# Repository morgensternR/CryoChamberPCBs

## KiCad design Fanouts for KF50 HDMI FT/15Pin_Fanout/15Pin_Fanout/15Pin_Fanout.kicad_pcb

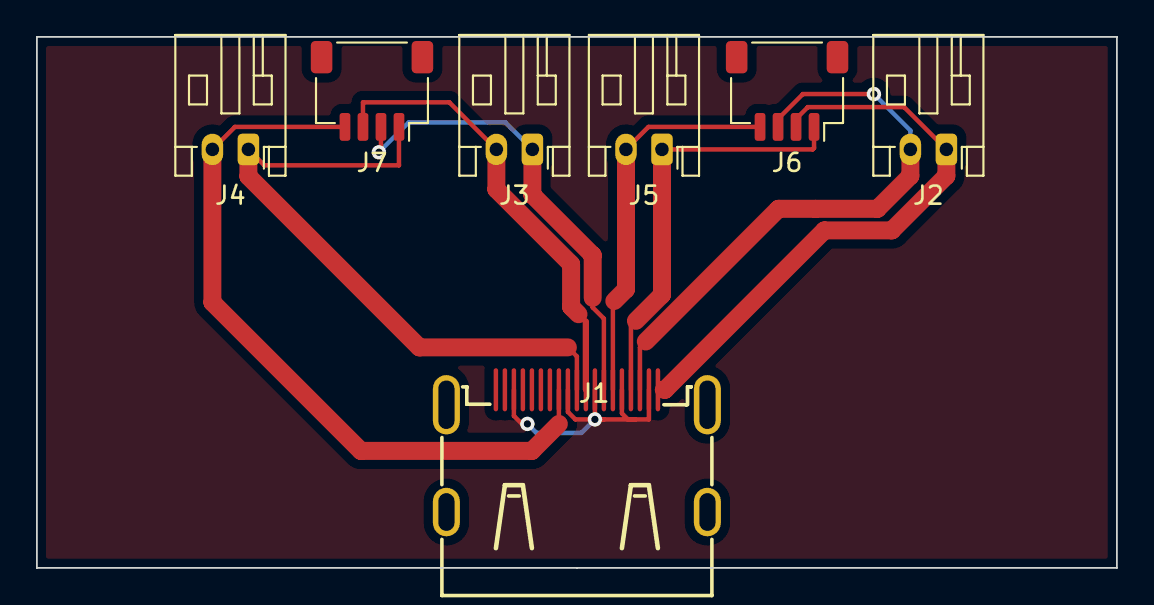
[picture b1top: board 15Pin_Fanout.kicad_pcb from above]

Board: 2 copper layers, 60.0 x 29.5 mm, 7 parts (0 on the bottom side), 9 nets.

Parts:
J1: HDMI_A; HDMI-SMD_HDMI-019S
J2, J3, J4, J5: Conn_01x02; JST_PH_S2B-PH-K_1x02_P2.00mm_Horizontal
J6, J7: Conn_01x04; JST_SH_SM04B-SRSS-TB_1x04-1MP_P1.00mm_Horizontal

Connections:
GND: J1.2 (D2S), J1.5 (D1S), J1.8 (D0S), J1.11 (CKS), J1.17 (GND)
unnamed: J1.1 (D2+), J2.1, J6.2
unnamed: J1.3 (D2-), J2.2, J6.3
unnamed: J1.4 (D1+), J5.1, J6.1
unnamed: J1.6 (D1-), J5.2, J6.4
unnamed: J1.7 (D0+), J3.1, J7.2
unnamed: J1.9 (D0-), J3.2, J7.3
unnamed: J1.10 (CK+), J4.1, J7.1
unnamed: J1.12 (CK-), J4.2, J7.4

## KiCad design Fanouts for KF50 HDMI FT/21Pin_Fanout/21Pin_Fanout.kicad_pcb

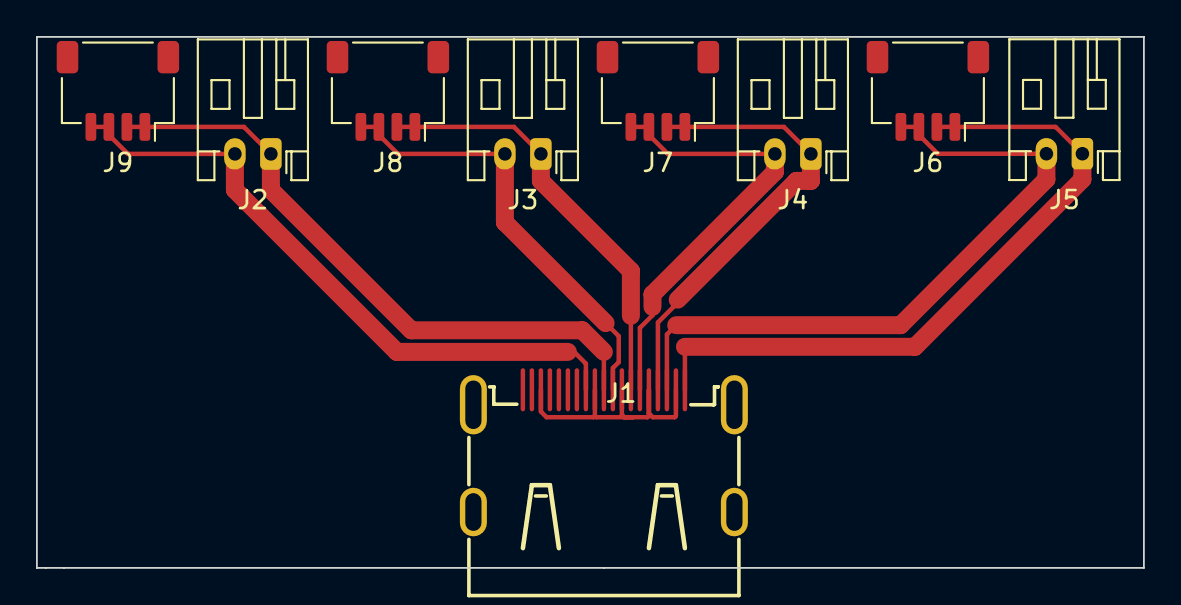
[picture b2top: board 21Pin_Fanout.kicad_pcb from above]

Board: 2 copper layers, 61.5 x 29.5 mm, 9 parts (0 on the bottom side), 9 nets.

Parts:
J1: HDMI_A; HDMI-SMD_HDMI-019S
J2, J3, J4, J5: Conn_01x02; JST_PH_S2B-PH-K_1x02_P2.00mm_Horizontal
J6, J7, J8, J9: Conn_01x04; JST_SH_SM04B-SRSS-TB_1x04-1MP_P1.00mm_Horizontal

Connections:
GND: J1.2 (D2S), J1.5 (D1S), J1.8 (D0S), J1.11 (CKS), J1.17 (GND)
unnamed: J1.1 (D2+), J5.1, J6.1, J6.2
unnamed: J1.3 (D2-), J5.2, J6.3, J6.4
unnamed: J1.4 (D1+), J4.1, J7.1, J7.2
unnamed: J1.6 (D1-), J4.2, J7.3, J7.4
unnamed: J1.7 (D0+), J3.1, J8.1, J8.2
unnamed: J1.9 (D0-), J3.2, J8.3, J8.4
unnamed: J1.10 (CK+), J2.1, J9.1, J9.2
unnamed: J1.12 (CK-), J2.2, J9.3, J9.4

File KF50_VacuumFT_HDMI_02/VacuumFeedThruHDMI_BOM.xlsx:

Comment | Designator | Footprint | LCSC
HDMI | J1 J2 J3 J4 J5 J6 J7 J8 J9 | Connector:HDMI-Vertical-Male-JLBPCB | C168715

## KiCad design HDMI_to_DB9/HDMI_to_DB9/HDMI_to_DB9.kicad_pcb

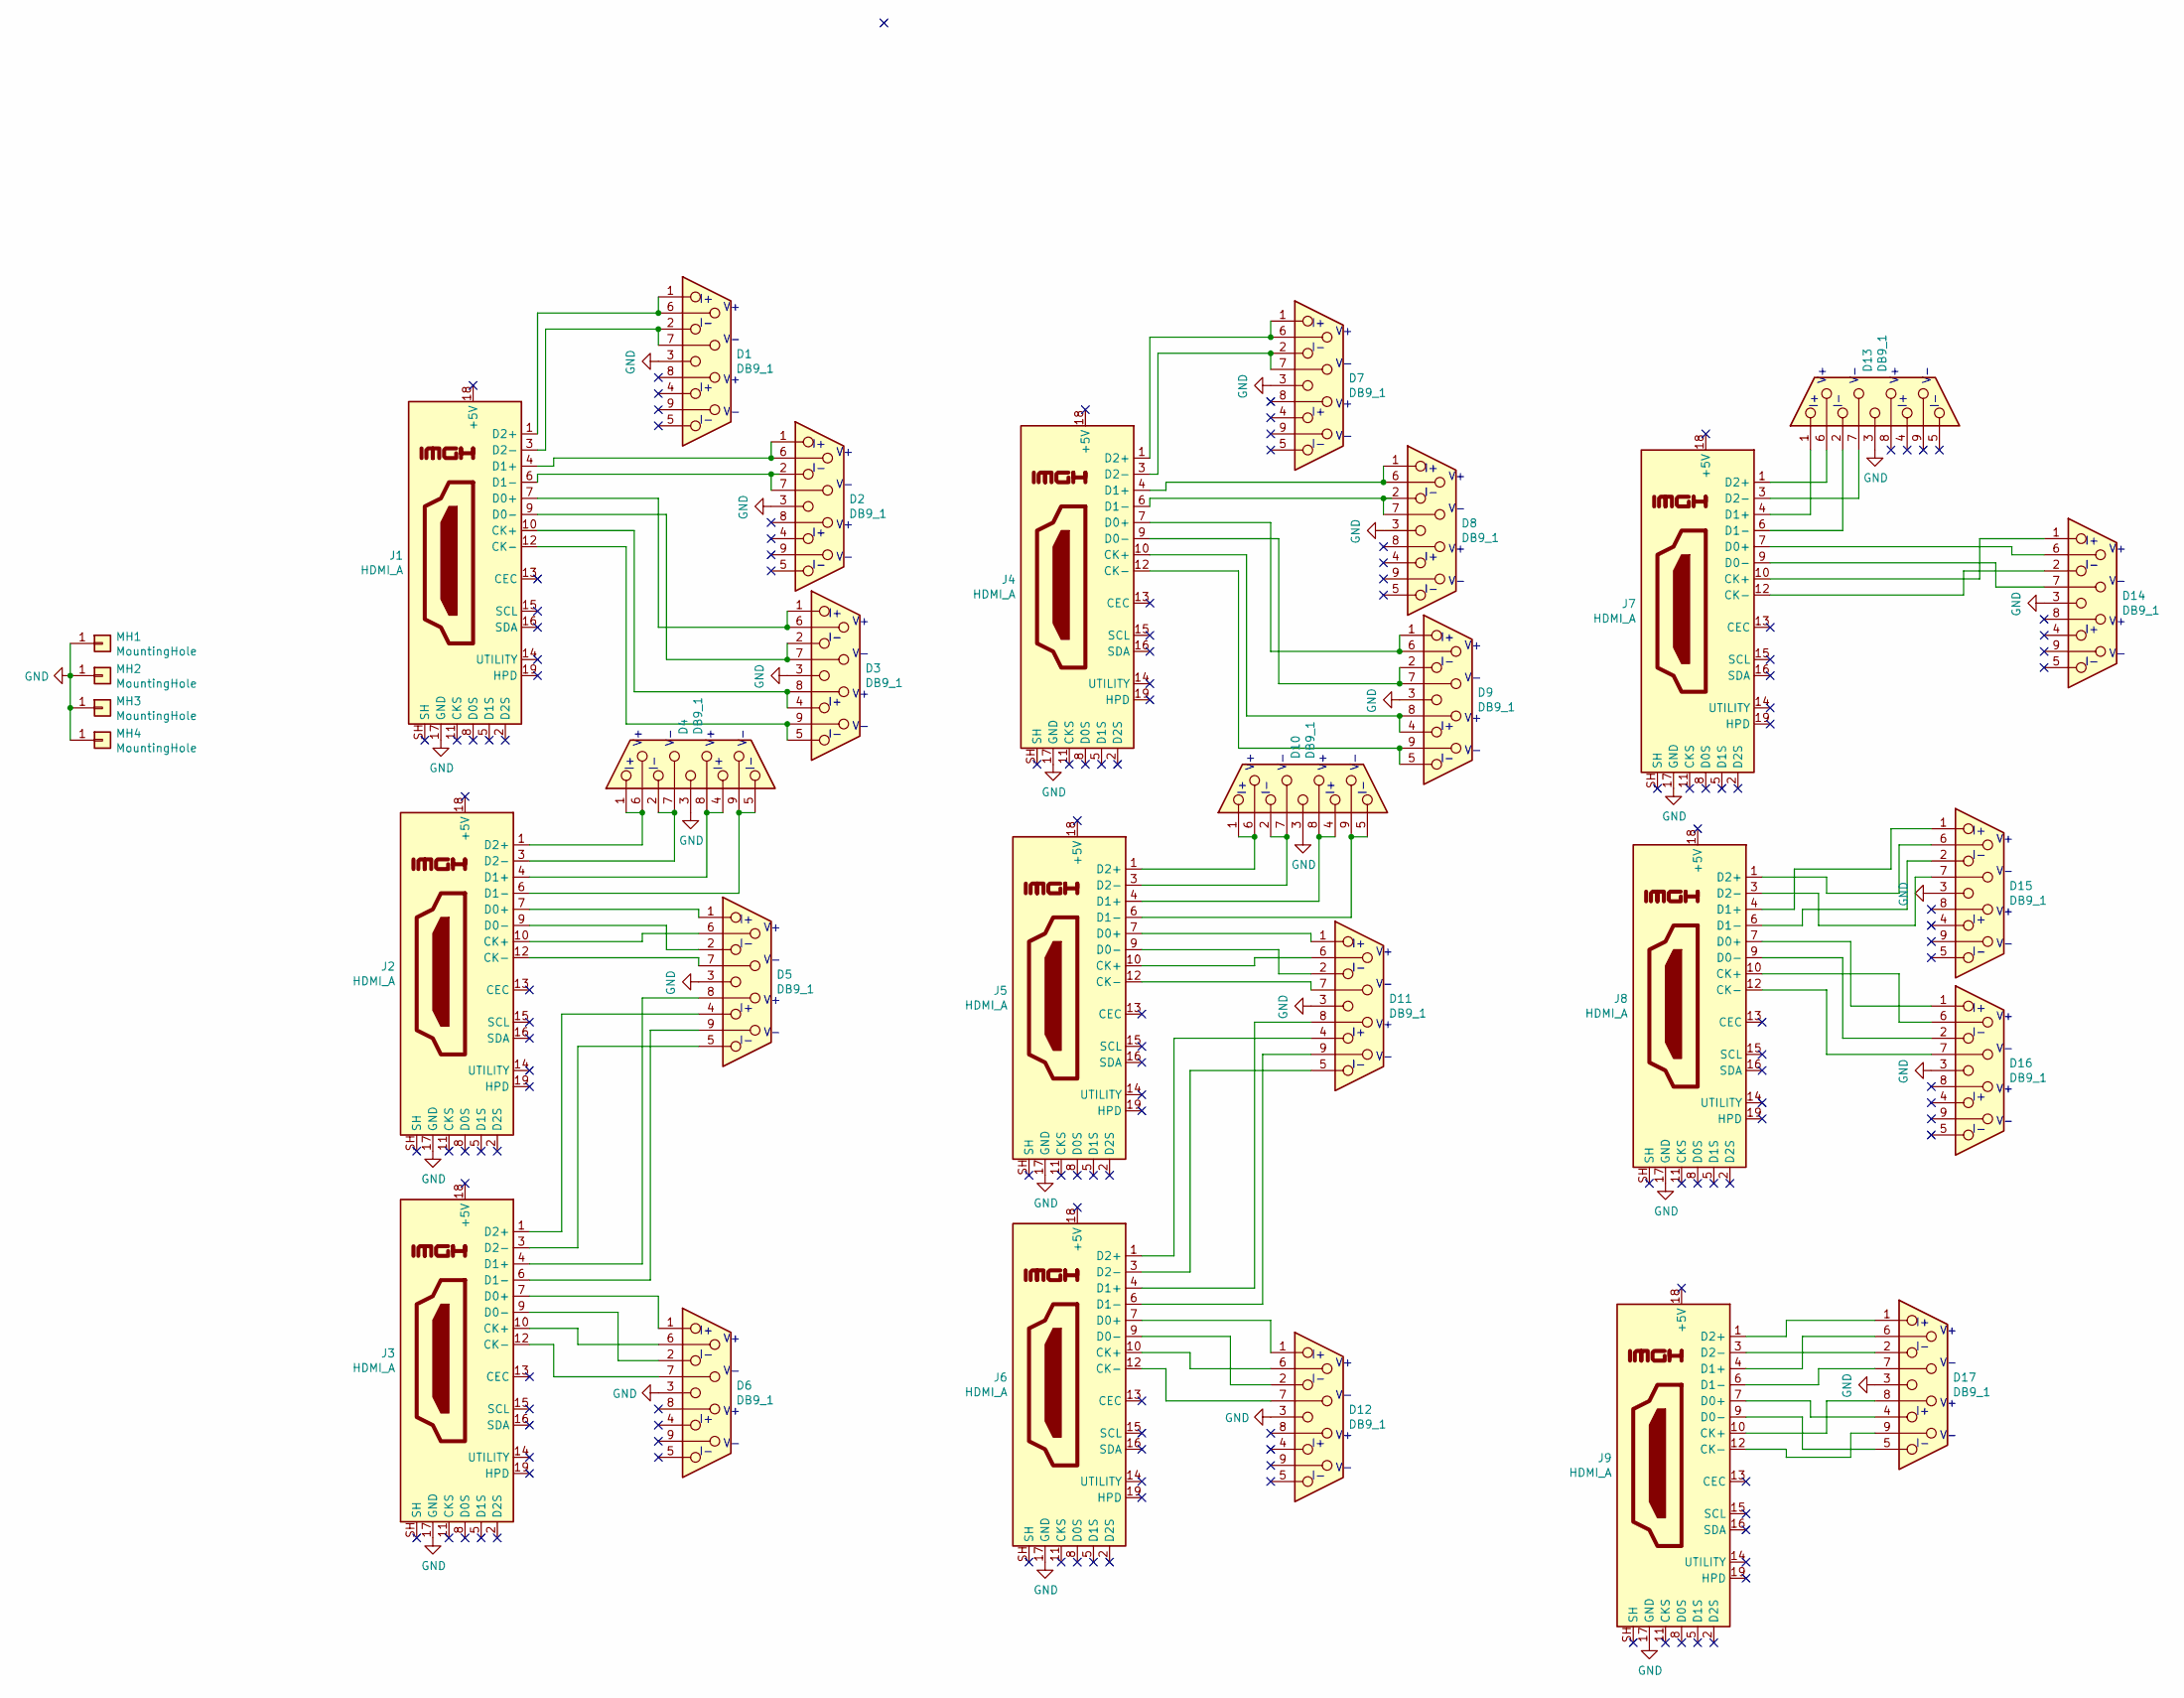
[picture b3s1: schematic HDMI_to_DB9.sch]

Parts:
D1, D2, D3, D4, D5, D6, D7, D8, D9, D10, D11, D12, D13, D14, D15, D16, D17: DB9_1; Vertical_DB9_Female; LCSC C77831
J1, J2, J3, J4, J5, J6, J7, J8, J9: HDMI_A; HDMI-SMD_A111926-B-01-R_Female; LCSC C720616
MH1, MH2, MH3, MH4: MountingHole; MountingHole_3.5mm_Pad

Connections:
unnamed: D1.1, D1.6, J1.1 (D2+)
unnamed: D1.2, D1.7, J1.3 (D2-)
unnamed: D2.1, D2.6, J1.4 (D1+)
unnamed: D2.2, D2.7, J1.6 (D1-)
unnamed: D3.1, D3.6, J1.7 (D0+)
unnamed: D3.2, D3.7, J1.9 (D0-)
unnamed: D3.4, D3.8, J1.10 (CK+)
unnamed: D3.5, D3.9, J1.12 (CK-)
unnamed: D4.1, D4.6, J2.1 (D2+)
unnamed: D4.2, D4.7, J2.3 (D2-)
unnamed: D4.4, D4.8, J2.4 (D1+)
unnamed: D4.5, D4.9, J2.6 (D1-)
unnamed: D5.1, J2.7 (D0+)
unnamed: D5.2, J2.9 (D0-)
unnamed: D5.4, J3.1 (D2+)
unnamed: D5.5, J3.3 (D2-)
unnamed: D5.6, J2.10 (CK+)
unnamed: D5.7, J2.12 (CK-)
unnamed: D5.8, J3.4 (D1+)
unnamed: D5.9, J3.6 (D1-)
unnamed: D6.1, J3.7 (D0+)
unnamed: D6.2, J3.9 (D0-)
unnamed: D6.6, J3.10 (CK+)
unnamed: D6.7, J3.12 (CK-)
unnamed: D7.1, D7.6, J4.1 (D2+)
unnamed: D7.2, D7.7, J4.3 (D2-)
unnamed: D8.1, D8.6, J4.4 (D1+)
unnamed: D8.2, D8.7, J4.6 (D1-)
unnamed: D9.1, D9.6, J4.7 (D0+)
unnamed: D9.2, D9.7, J4.9 (D0-)
unnamed: D9.4, D9.8, J4.10 (CK+)
unnamed: D9.5, D9.9, J4.12 (CK-)
unnamed: D10.1, D10.6, J5.1 (D2+)
unnamed: D10.2, D10.7, J5.3 (D2-)
unnamed: D10.4, D10.8, J5.4 (D1+)
unnamed: D10.5, D10.9, J5.6 (D1-)
unnamed: D11.1, J5.7 (D0+)
unnamed: D11.2, J5.9 (D0-)
unnamed: D11.4, J6.1 (D2+)
unnamed: D11.5, J6.3 (D2-)
unnamed: D11.6, J5.10 (CK+)
unnamed: D11.7, J5.12 (CK-)
unnamed: D11.8, J6.4 (D1+)
unnamed: D11.9, J6.6 (D1-)
unnamed: D12.1, J6.7 (D0+)
unnamed: D12.2, J6.9 (D0-)
unnamed: D12.6, J6.10 (CK+)
unnamed: D12.7, J6.12 (CK-)
unnamed: D13.1, J7.4 (D1+)
unnamed: D13.2, J7.6 (D1-)
unnamed: D13.6, J7.1 (D2+)
unnamed: D13.7, J7.3 (D2-)
unnamed: D14.1, J7.10 (CK+)
unnamed: D14.2, J7.12 (CK-)
unnamed: D14.6, J7.7 (D0+)
unnamed: D14.7, J7.9 (D0-)
unnamed: D15.1, J8.4 (D1+)
unnamed: D15.2, J8.6 (D1-)
unnamed: D15.6, J8.1 (D2+)
unnamed: D15.7, J8.3 (D2-)
unnamed: D16.1, J8.7 (D0+)
unnamed: D16.2, J8.9 (D0-)
unnamed: D16.6, J8.10 (CK+)
unnamed: D16.7, J8.12 (CK-)
unnamed: D17.1, J9.1 (D2+)
unnamed: D17.2, J9.3 (D2-)
unnamed: D17.4, J9.7 (D0+)
unnamed: D17.5, J9.9 (D0-)
unnamed: D17.6, J9.4 (D1+)
unnamed: D17.7, J9.6 (D1-)
unnamed: D17.8, J9.10 (CK+)
unnamed: D17.9, J9.12 (CK-)

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
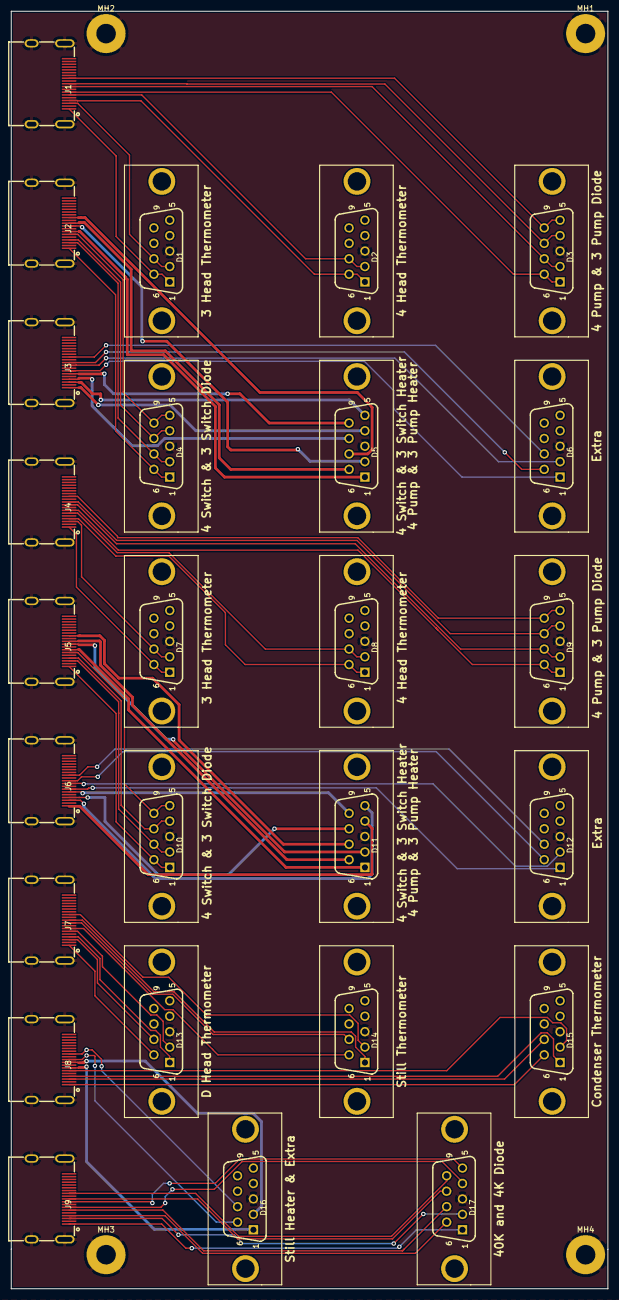
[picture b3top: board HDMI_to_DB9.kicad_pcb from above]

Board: 2 copper layers, 107.0 x 229.1 mm, 30 parts (0 on the bottom side), 73 nets.

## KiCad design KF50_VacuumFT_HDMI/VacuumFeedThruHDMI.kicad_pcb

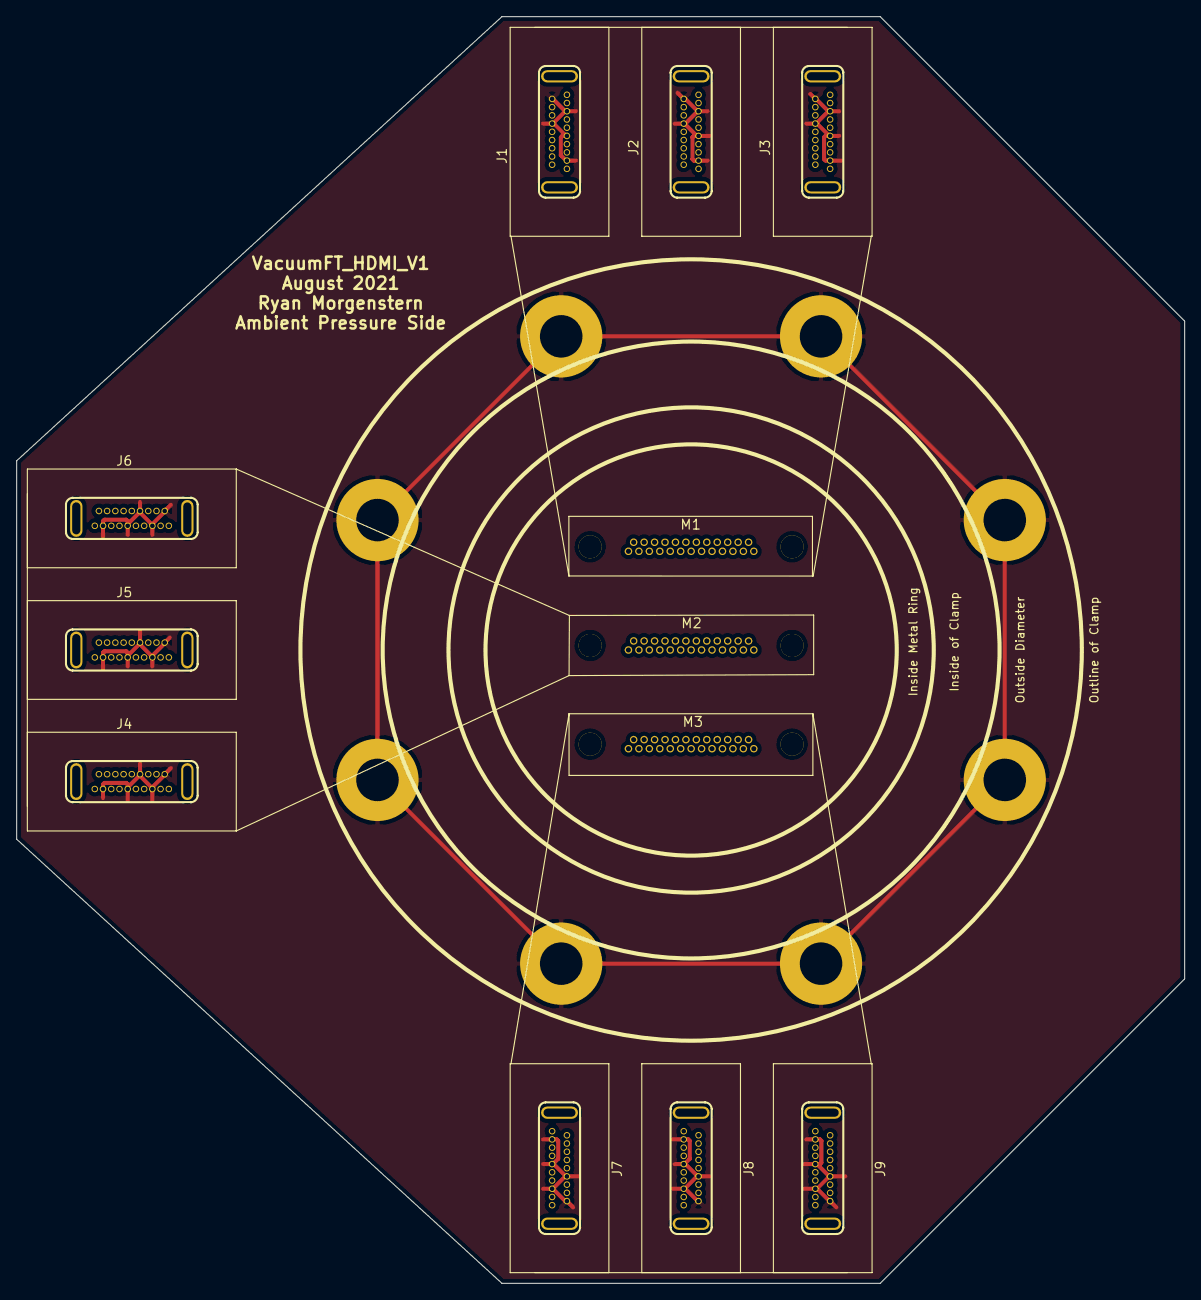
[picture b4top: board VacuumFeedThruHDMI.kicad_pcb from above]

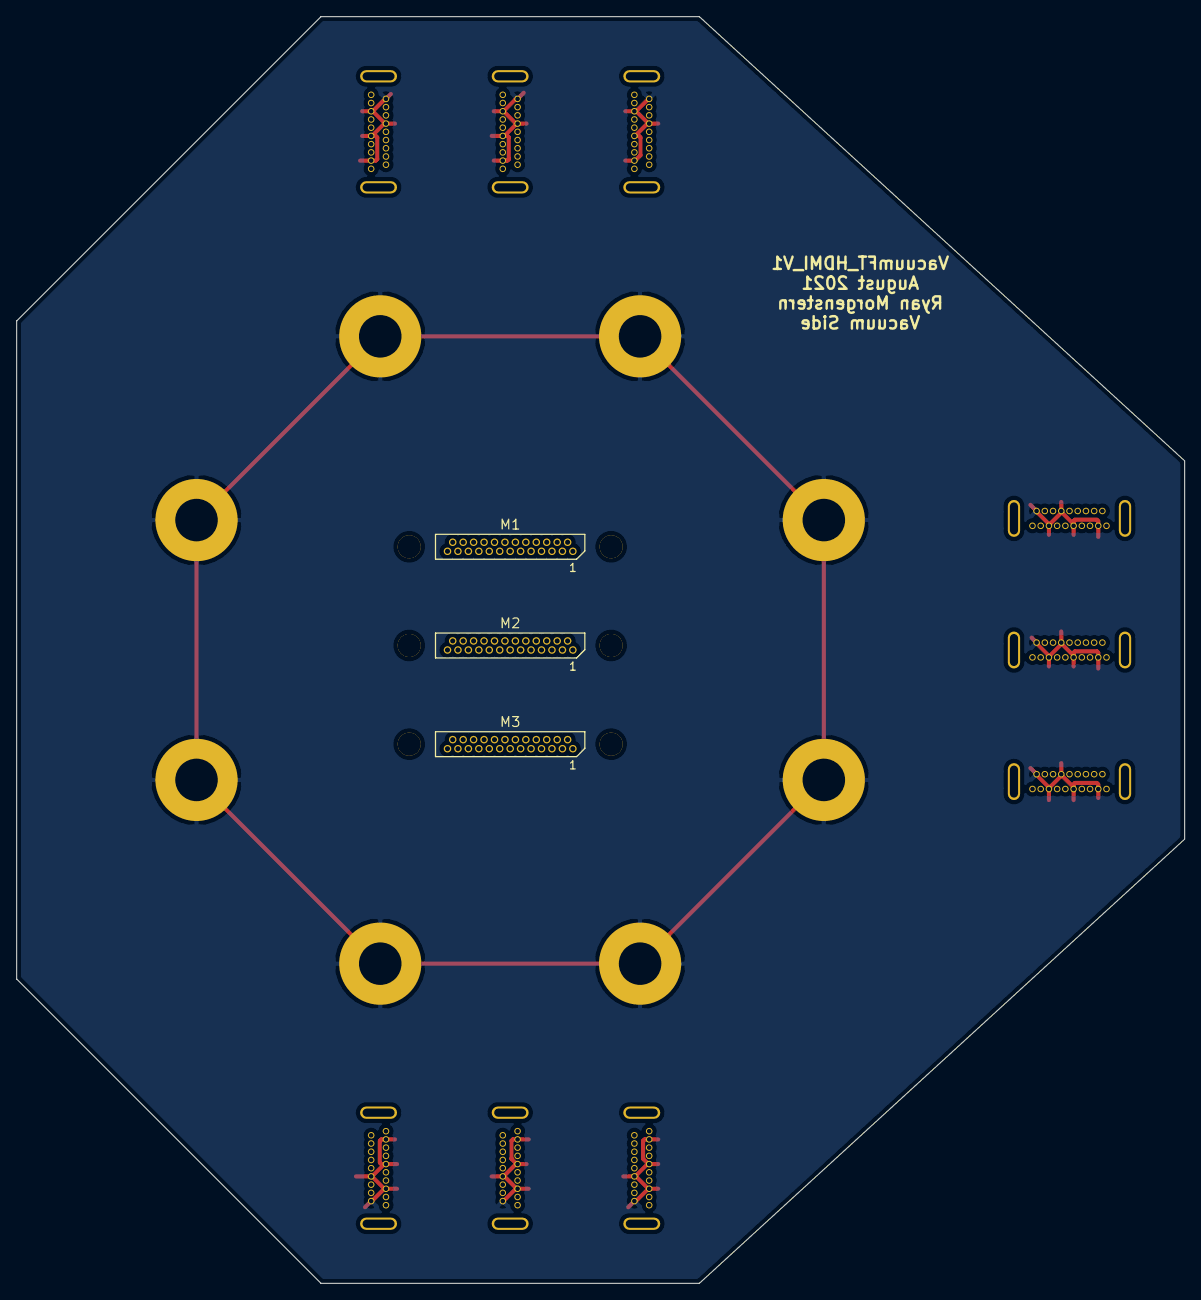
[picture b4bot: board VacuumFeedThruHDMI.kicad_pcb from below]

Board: 4 copper layers, 142.0 x 154.0 mm, 13 parts (3 on the bottom side), 73 nets.

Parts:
J1, J2, J3, J4, J5, J6, J7, J8, J9: HDMI_A_1.4; HDMI-Vertical-Male-JLBPCB
M1, M2, M3: DB25_Male; Norcomp-380-025-113L001-microd_NoLeads
M2#2: Conn_01x08; KF50_Print

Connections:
GND: J1.2, J1.5, J1.8, J1.11, J1.17, J2.2, J2.5, J2.8, J2.11, J2.17, J3.2, J3.5, J3.8, J3.11, J3.17, J4.2, J4.5, J4.8, J4.11, J4.17, J5.2, J5.5, J5.8, J5.11, J5.17, J6.2, J6.5, J6.8, J6.11, J6.17, J7.2, J7.5, J7.8, J7.11, J7.17, J8.2, J8.5, J8.8, J8.11, J8.17, J9.2, J9.5, J9.8, J9.11, J9.17, M2#2.1, M2#2.2, M2#2.3, M2#2.4, M2#2.5, M2#2.6, M2#2.7, M2#2.8
unnamed: J1.1, M1.1
unnamed: J1.3, M1.14
unnamed: J1.4, M1.2
unnamed: J1.6, M1.15
unnamed: J1.7, M1.3
unnamed: J1.9, M1.16
unnamed: J1.10, M1.4
unnamed: J1.12, M1.17
unnamed: J2.1, M1.5
unnamed: J2.3, M1.18
unnamed: J2.4, M1.6
unnamed: J2.6, M1.19
unnamed: J2.7, M1.7
unnamed: J2.9, M1.20
unnamed: J2.10, M1.8
unnamed: J2.12, M1.21
unnamed: J3.1, M1.9
unnamed: J3.3, M1.22
unnamed: J3.4, M1.10
unnamed: J3.6, M1.23
unnamed: J3.7, M1.11
unnamed: J3.9, M1.24
unnamed: J3.10, M1.12
unnamed: J3.12, M1.25
unnamed: J4.1, M2.1
unnamed: J4.3, M2.14
unnamed: J4.4, M2.2
unnamed: J4.6, M2.15
unnamed: J4.7, M2.3
unnamed: J4.9, M2.16
unnamed: J4.10, M2.4
unnamed: J4.12, M2.17
unnamed: J5.1, M2.5
unnamed: J5.3, M2.18
unnamed: J5.4, M2.6
unnamed: J5.6, M2.19
unnamed: J5.7, M2.7
unnamed: J5.9, M2.20
unnamed: J5.10, M2.8
unnamed: J5.12, M2.21
unnamed: J6.1, M2.9
unnamed: J6.3, M2.22
unnamed: J6.4, M2.10
unnamed: J6.6, M2.23
unnamed: J6.7, M2.11
unnamed: J6.9, M2.24
unnamed: J6.10, M2.12
unnamed: J6.12, M2.25
unnamed: J7.1, M3.1
unnamed: J7.3, M3.14
unnamed: J7.4, M3.2
unnamed: J7.6, M3.15
unnamed: J7.7, M3.3
unnamed: J7.9, M3.16
unnamed: J7.10, M3.4
unnamed: J7.12, M3.17
unnamed: J8.1, M3.5
unnamed: J8.3, M3.18
unnamed: J8.4, M3.6
unnamed: J8.6, M3.19
unnamed: J8.7, M3.7
unnamed: J8.9, M3.20
unnamed: J8.10, M3.8
unnamed: J8.12, M3.21
unnamed: J9.1, M3.9
unnamed: J9.3, M3.22
unnamed: J9.4, M3.10
unnamed: J9.6, M3.23
unnamed: J9.7, M3.11
unnamed: J9.9, M3.24
unnamed: J9.10, M3.12
unnamed: J9.12, M3.25

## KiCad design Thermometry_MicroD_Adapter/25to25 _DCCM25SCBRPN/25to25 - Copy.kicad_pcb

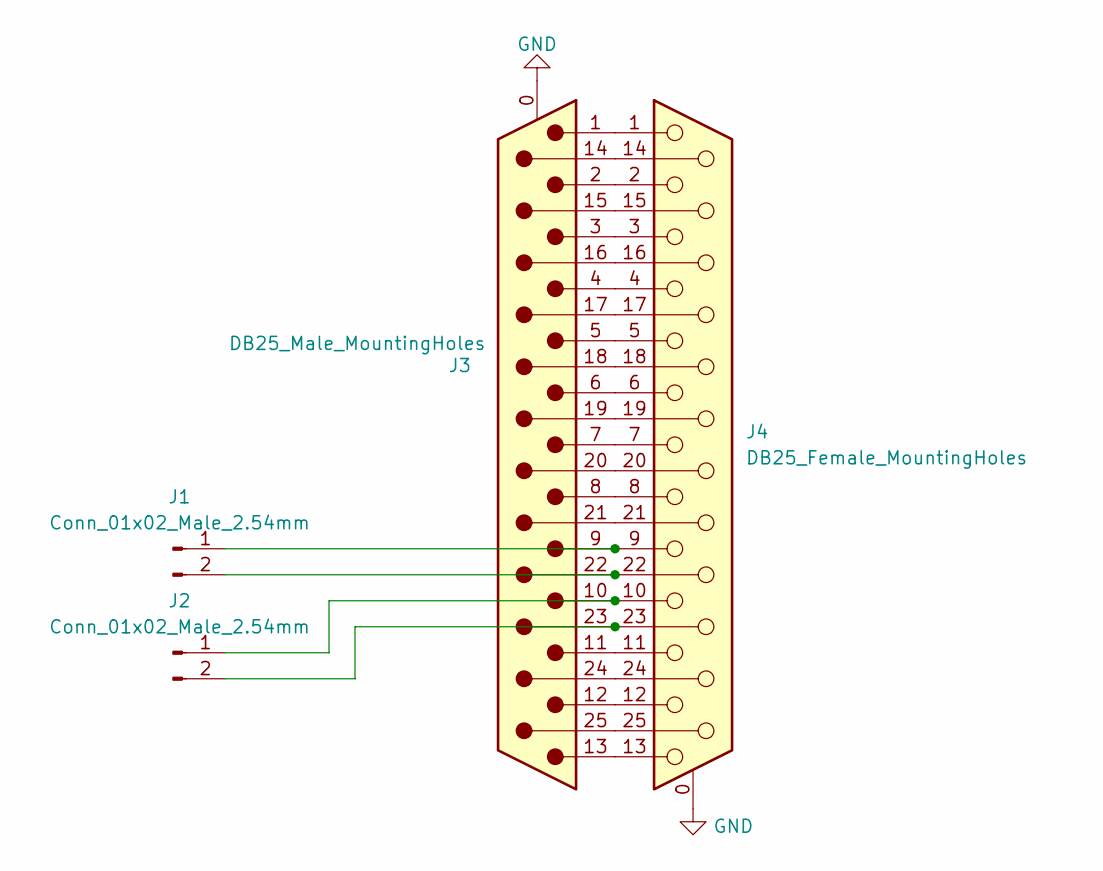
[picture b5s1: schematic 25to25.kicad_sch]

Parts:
J1, J2: Conn_01x02_Male_2.54mm; PinHeader_1x02_P2.54mm_Horizontal; MPN PZ254V-11-02P; LCSC C492401
J3: DB25_Male_MountingHoles; 381-025-112L565
J4: DB25_Female_MountingHoles; CINCH_DCCM25SCBRPN_Female

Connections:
GND: J3.0 (PAD), J4.0 (PAD)
unnamed: J1.1, J3.9, J4.9
unnamed: J1.2, J3.22, J4.22
unnamed: J2.1, J3.10, J4.10
unnamed: J2.2, J3.23, J4.23
unnamed: J3.1, J4.1
unnamed: J3.2, J4.2
unnamed: J3.3, J4.3
unnamed: J3.4, J4.4
unnamed: J3.5, J4.5
unnamed: J3.6, J4.6
unnamed: J3.7, J4.7
unnamed: J3.8, J4.8
unnamed: J3.11, J4.11
unnamed: J3.12, J4.12
unnamed: J3.13, J4.13
unnamed: J3.14, J4.14
unnamed: J3.15, J4.15
unnamed: J3.16, J4.16
unnamed: J3.17, J4.17
unnamed: J3.18, J4.18
unnamed: J3.19, J4.19
unnamed: J3.20, J4.20
unnamed: J3.21, J4.21
unnamed: J3.24, J4.24
unnamed: J3.25, J4.25

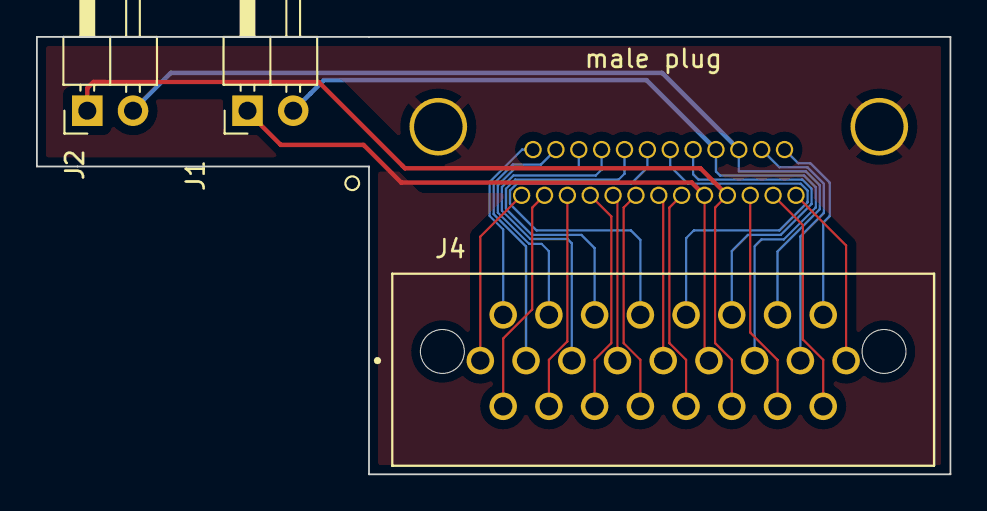
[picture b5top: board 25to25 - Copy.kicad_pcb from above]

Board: 2 copper layers, 50.8 x 24.3 mm, 4 parts (1 on the bottom side), 25 nets.

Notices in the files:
parts and their libraries:
Copyright 2021 Accelerated Designs. All rights reserved.
